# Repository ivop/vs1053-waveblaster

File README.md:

#VLSi SynthRoarer -- A vs1053/vs8053-waveblaster module
-------------------------------------------------
By using a vs1053/vs8053, we present to you an ideal, low-cost, easy to solder, some what compact and open source WaveBlaster module.
_________________________________________________
Introducing VLSi SynthRoarer.

*Support General Midi with 128 GM1 instruments 61 GM2 Bank 0 precussion sounds up to 64 notes polyphony and stereo output @48Khz 16bit

How's it sound?
--------------
Here is a sample from chip manufacture.

http://www.vlsi.fi/fileadmin/software/VS10XX/vs1053mid.mp3

Notes
------------------------
It's been tested on a old ESS 688 audiodrive sound card.

REV B and REV A is in gergber/old stable.7z

REV C IS BASICALLY REV B,their schematic is the same.

REV A = vs1053-waveblaster

REV C = vs1053-waveblaster-se

Pictures
----------------------------
Here's a view of it been fully assembled and not been. (It says REV C, but it's actually REV B).

*Look,it is working on my soundcard.

*a. It is your choice to use crystal or oscillator.

*b. Both vs8053 and vs1053 can be used. There're no diffience in the MIDI implementation. Just buy the cheapest one.

*All values are printed on the silkscreen.

Check out another waveblaster project: https://github.com/ivop/cs9236-waveblaster

What's next?
------------------------------
1.Fully SMT-ized?(Maybe REV D?)

2.Get a proper logo?(Maybe REV D?)

3.Write a bom list?(How about right now!)

License
-----------------
<br />This work is licensed under a <a rel="license" href="http://creativecommons.org/licenses/by-sa/4.0/">Creative Commons Attribution-ShareAlike 4.0 International License</a>.

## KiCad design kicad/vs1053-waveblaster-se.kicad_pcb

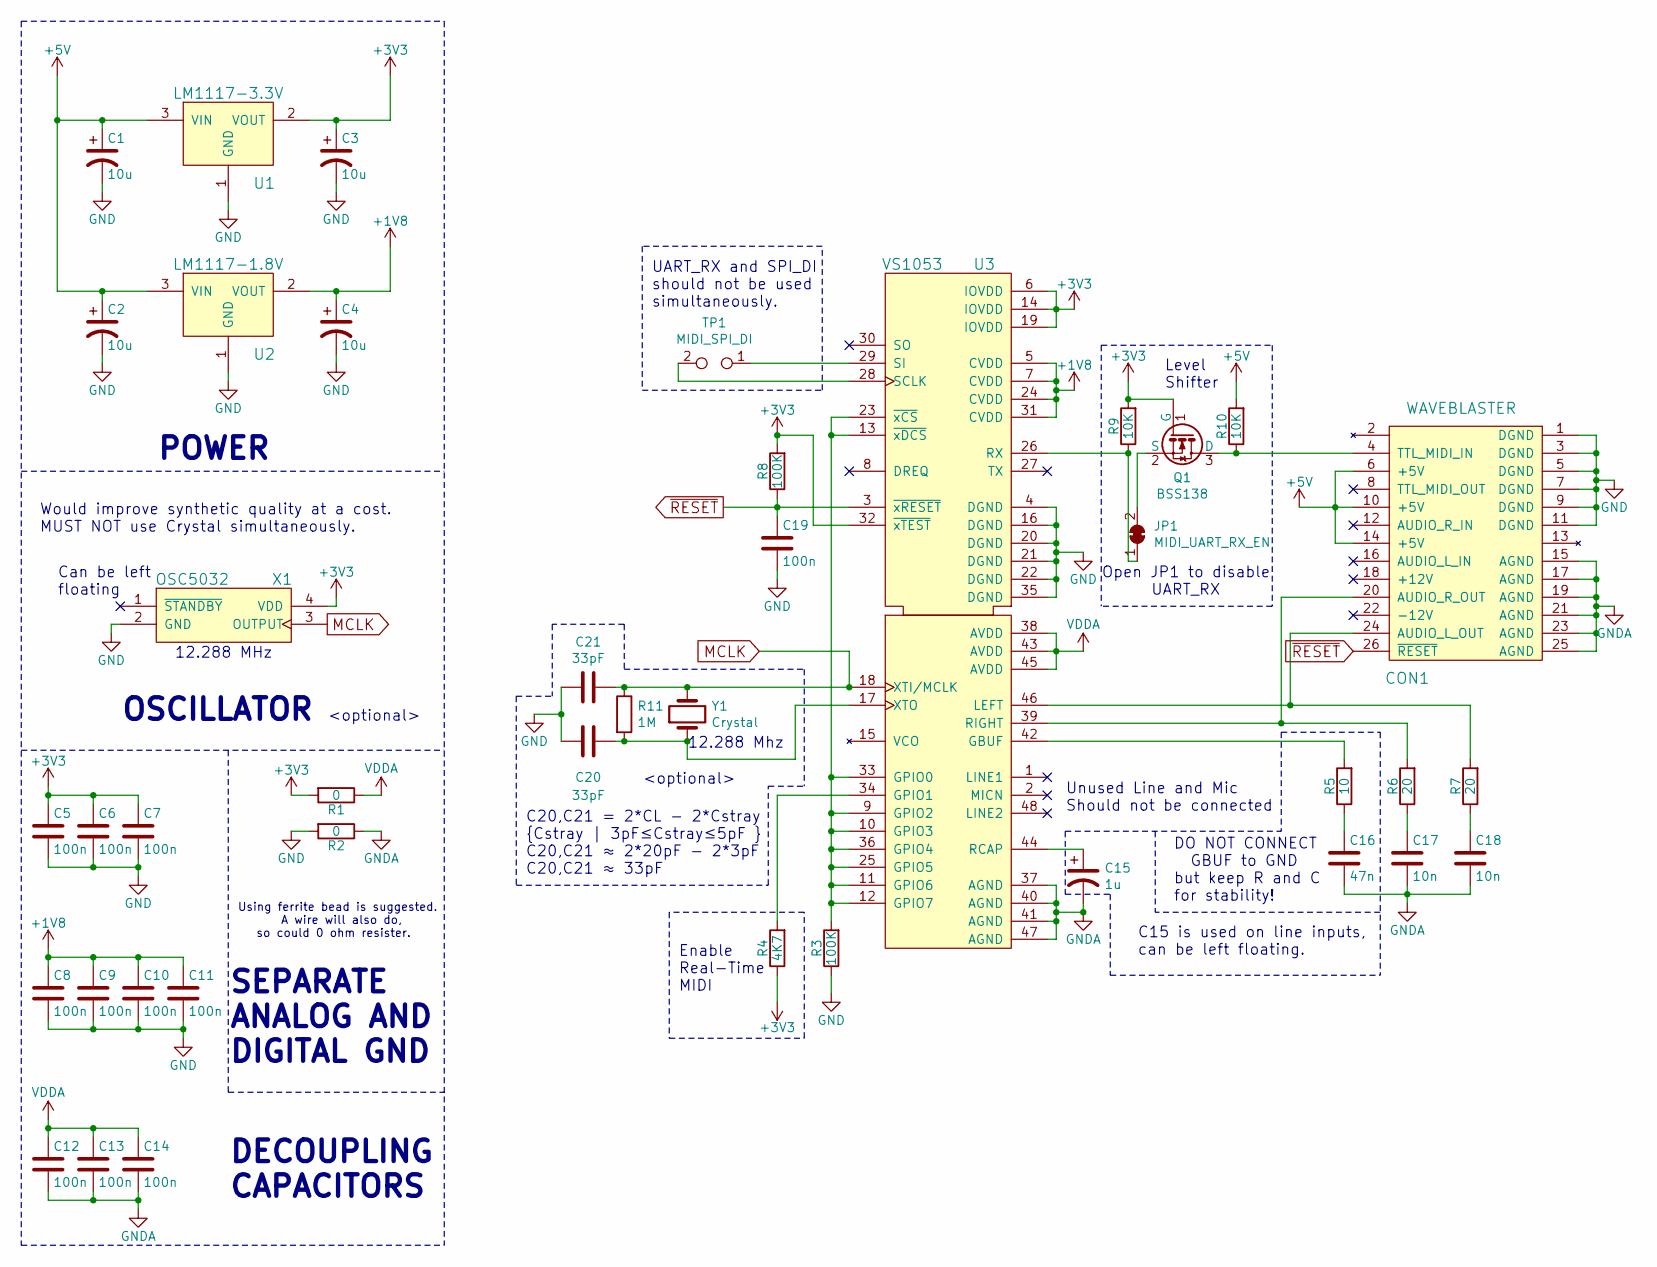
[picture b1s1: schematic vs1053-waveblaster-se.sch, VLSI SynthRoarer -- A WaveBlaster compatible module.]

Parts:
C1, C2, C3, C4: 10u; CP_Radial_D5.0mm_P2.50mm
C5, C6, C7, C8, C9, C10, C11, C12, C13, C14, C19: 100n; C_Disc_D3.0mm_W1.6mm_P2.50mm
C15: 1u; C_Disc_D3.0mm_W1.6mm_P2.50mm
C16: 47n; C_Disc_D3.0mm_W1.6mm_P2.50mm
C17, C18: 10n; C_Disc_D3.0mm_W1.6mm_P2.50mm
C20, C21: 33pF; C_Disc_D3.0mm_W1.6mm_P2.50mm
CON1: WAVEBLASTER; PinHeader_2x13_P2.54mm_Vertical
JP1: MIDI_UART_RX_EN; SolderJumper-2_P1.3mm_Bridged2Bar_RoundedPad1.0x1.5mm
Q1: BSS138; SOT-23
R1, R2: 0; R_Axial_DIN0207_L6.3mm_D2.5mm_P10.16mm_Horizontal
R3, R8: 100K; R_Axial_DIN0207_L6.3mm_D2.5mm_P10.16mm_Horizontal
R4: 4K7; R_Axial_DIN0207_L6.3mm_D2.5mm_P10.16mm_Horizontal
R5: 10; R_Axial_DIN0207_L6.3mm_D2.5mm_P10.16mm_Horizontal
R6, R7: 20; R_Axial_DIN0207_L6.3mm_D2.5mm_P10.16mm_Horizontal
R9, R10: 10K; R_Axial_DIN0207_L6.3mm_D2.5mm_P10.16mm_Horizontal
R11: 1M; R_Axial_DIN0207_L6.3mm_D2.5mm_P10.16mm_Horizontal
TP1: MIDI_SPI_DI; PinSocket_1x02_P2.54mm_Vertical
U1: LM1117-3.3V; SOT-223
U2: LM1117-1.8V; SOT-223
U3: VS1053; LQFP-48-1EP_7x7mm_P0.5mm_EP3.6x3.6mm
X1: OSC5032; Crystal_SMD_5032-4Pin_5.0x3.2mm
Y1: Crystal; Crystal_HC49-U_Vertical

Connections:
+1V8: C4.1, C8.1, C9.1, C10.1, C11.1, U2.2 (VOUT), U3.5 (CVDD), U3.7 (CVDD), U3.24 (CVDD), U3.31 (CVDD)
+3V3: C3.1, C5.1, C6.1, C7.1, Q1.1 (G), R1.2, R4.1, R8.2, R9.2, U1.2 (VOUT), U3.6 (IOVDD), U3.14 (IOVDD), U3.19 (IOVDD), U3.32 (~xTEST), X1.4 (VDD)
+5V: C1.1, C2.1, CON1.6 (+5V), CON1.10 (+5V), CON1.14 (+5V), R10.2, U1.3 (VIN), U2.3 (VIN)
GND: C1.2, C2.2, C3.2, C4.2, C5.2, C6.2, C7.2, C8.2, C9.2, C10.2, C11.2, C19.2, C20.1, C21.1, CON1.1 (DGND), CON1.3 (DGND), CON1.5 (DGND), CON1.7 (DGND), CON1.9 (DGND), CON1.11 (DGND), R2.2, R3.1, U1.1 (GND), U2.1 (GND), U3.4 (DGND), U3.16 (DGND), U3.20 (DGND), U3.21 (DGND), U3.22 (DGND), U3.35 (DGND), X1.2 (GND)
GNDA: C12.2, C13.2, C14.2, C15.2, C16.2, C17.2, C18.2, CON1.15 (AGND), CON1.17 (AGND), CON1.19 (AGND), CON1.21 (AGND), CON1.23 (AGND), CON1.25 (AGND), R2.1, U3.37 (AGND), U3.40 (AGND), U3.41 (AGND), U3.47 (AGND)
MCLK: C21.2, R11.1, U3.18 (XTI/MCLK), X1.3 (OUTPUT), Y1.2
unnamed: C15.1, U3.44 (RCAP)
unnamed: C16.1, R5.1
unnamed: C17.1, R6.1
unnamed: C18.1, R7.1
unnamed: C20.2, R11.2, U3.17 (XTO), Y1.1
unnamed: CON1.4 (TTL_MIDI_IN), Q1.3 (D), R10.1
unnamed: CON1.20 (AUDIO_R_OUT), R6.2, U3.39 (RIGHT)
unnamed: CON1.24 (AUDIO_L_OUT), R7.2, U3.46 (LEFT)
unnamed: JP1.1 (A), R9.1, U3.26 (RX)
unnamed: JP1.2 (B), Q1.2 (S)
unnamed: R3.2, U3.9 (GPIO2), U3.10 (GPIO3), U3.11 (GPIO6), U3.12 (GPIO7), U3.13 (~xDCS), U3.23 (~xCS), U3.25 (GPIO5), U3.33 (GPIO0), U3.36 (GPIO4)
unnamed: R4.2, U3.34 (GPIO1)
unnamed: R5.2, U3.42 (GBUF)
unnamed: TP1.1, U3.29 (SI)
unnamed: TP1.2, U3.28 (SCLK)
VDDA: C12.1, C13.1, C14.1, R1.1, U3.38 (AVDD), U3.43 (AVDD), U3.45 (AVDD)
~RESET: C19.1, CON1.26 (~RESET), R8.1, U3.3 (~xRESET)

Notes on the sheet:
Enable Real-Time MIDI
Unused Line and Mic Should not be connected
DO NOT CONNECT GBUF to GND but keep R and C for stability!
12.288 MHz
Can be left floating
POWER
DECOUPLING CAPACITORS
SEPARATE ANALOG AND DIGITAL GND
UART_RX and SPI_DI should not be used simultaneously.
12.288 Mhz
OSCILLATOR
<optional>
Would improve synthetic quality at a cost. MUST NOT use Crystal simultaneously.
Using ferrite bead is suggested. A wire will also do, so could 0 ohm resister.
C20,C21 = 2*CL - 2*Cstray {Cstray | 3pF≤Cstray≤5pF } C20,C21 ≈ 2*20pF - 2*3pF C20,C21 ≈ 33pF
Level Shifter
Open JP1 to disable UART_RX
C15 is used on line inputs, can be left floating.

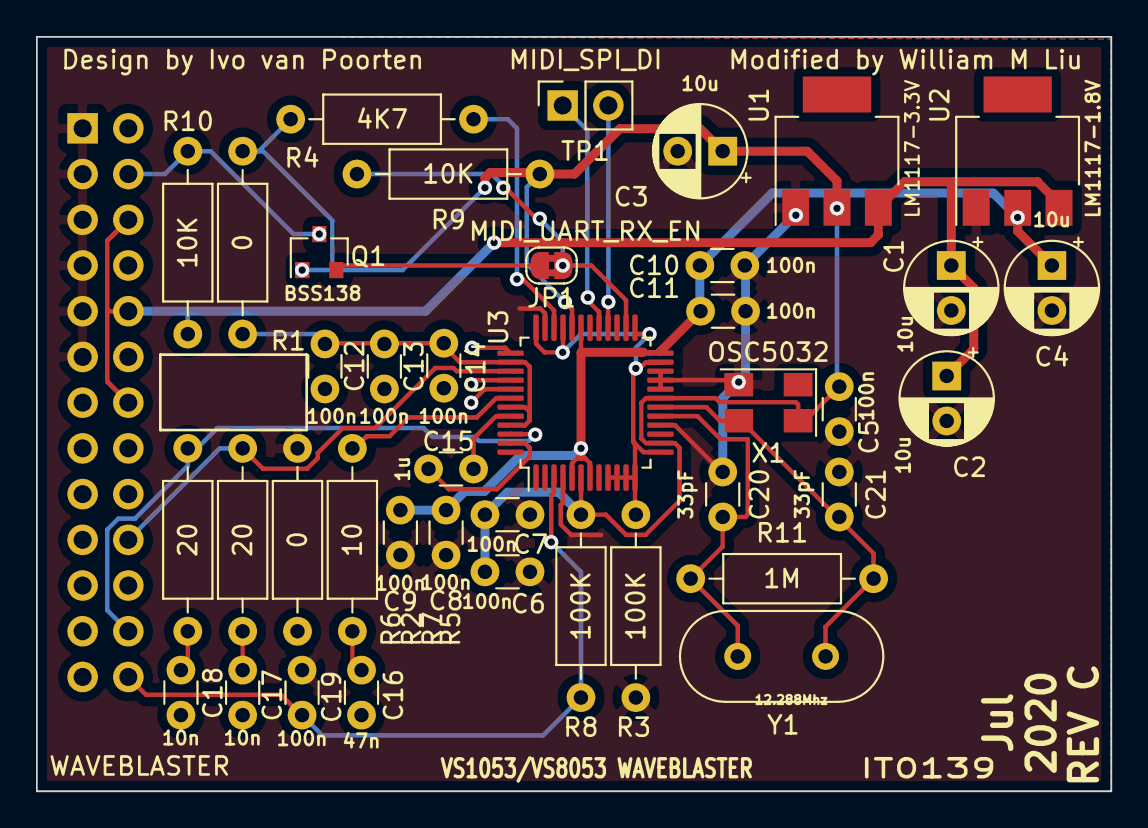
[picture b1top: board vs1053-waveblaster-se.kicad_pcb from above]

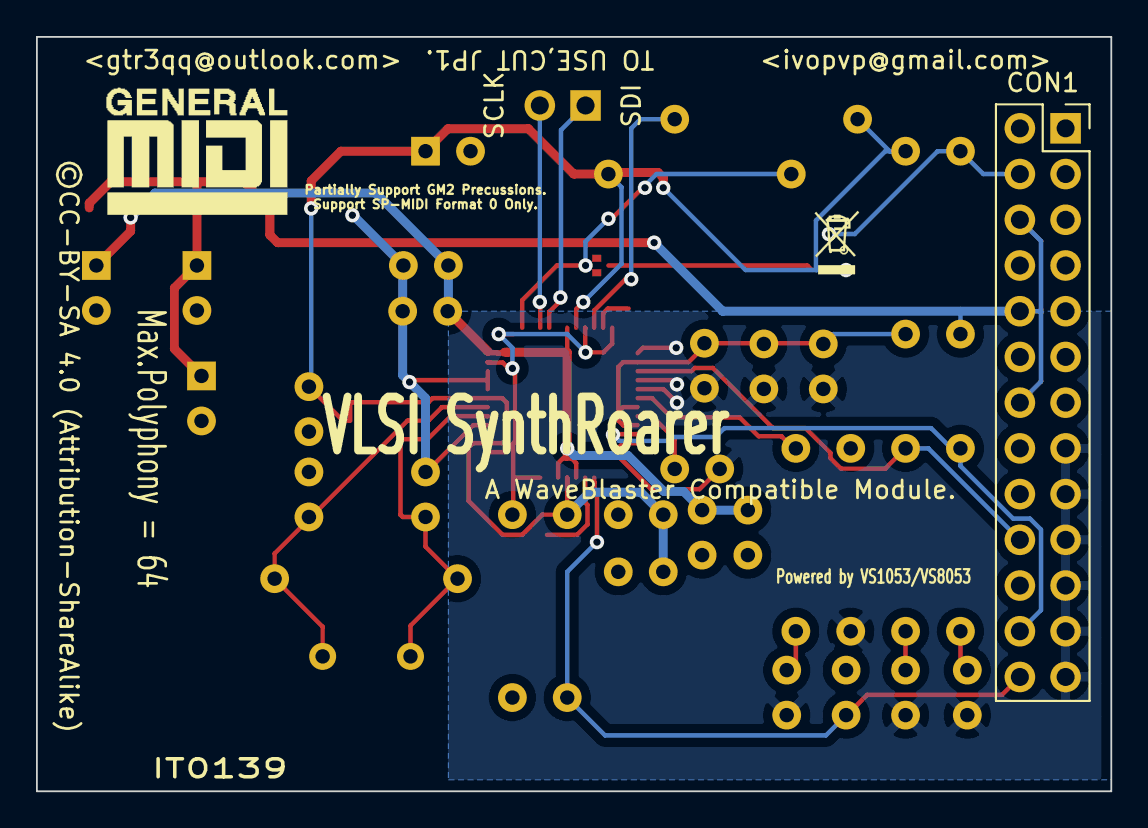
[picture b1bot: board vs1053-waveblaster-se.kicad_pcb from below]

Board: 2 copper layers, 59.7 x 41.9 mm, 43 parts (3 on the bottom side), 23 nets.

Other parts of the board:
G1: LOGO; logo_unrecl
G2: LOGO; logo_GM

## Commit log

2019-09-02 new VS1053 based WaveBlaster daughterboard
2019-09-02 link to other WB board
2020-12-31 Parched a few minor error to get it to work.
2020-12-31 Create LICENSE
2020-12-31 Some picture of it
2020-12-31 Update LICENSE
2021-01-14 Fix some typos and formatting.
2021-01-14 the PCB says REV A, but it is actually REV B
2021-01-14 PCB says both A and C, but it is actually REV B i.e. reverse previous commit
2021-01-15 fix spelling error and call it a module

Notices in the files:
kicad/vs1053-waveblaster-se.kicad_pcb:
© CC-BY-SA 4.0
©CC-BY-SA 4.0 (Attribution-ShareAlike)
